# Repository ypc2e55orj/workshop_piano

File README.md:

# 簡易ピアノ

2024/01/11, Kohei Hayashi

## ディレクトリ構成

| フォルダ名 |         説明         |
| :--------: | :------------------: |
|  firmware  | MPLAB X プロジェクト |
| schematic  |  KiCad プロジェクト  |
|    docs    |         資料         |

## 必要バージョン

- MPLAB X IDE `v6.15`, xc8 `v2.45`
- KiCad `7.0`
- Microsoft Office 365 Excel

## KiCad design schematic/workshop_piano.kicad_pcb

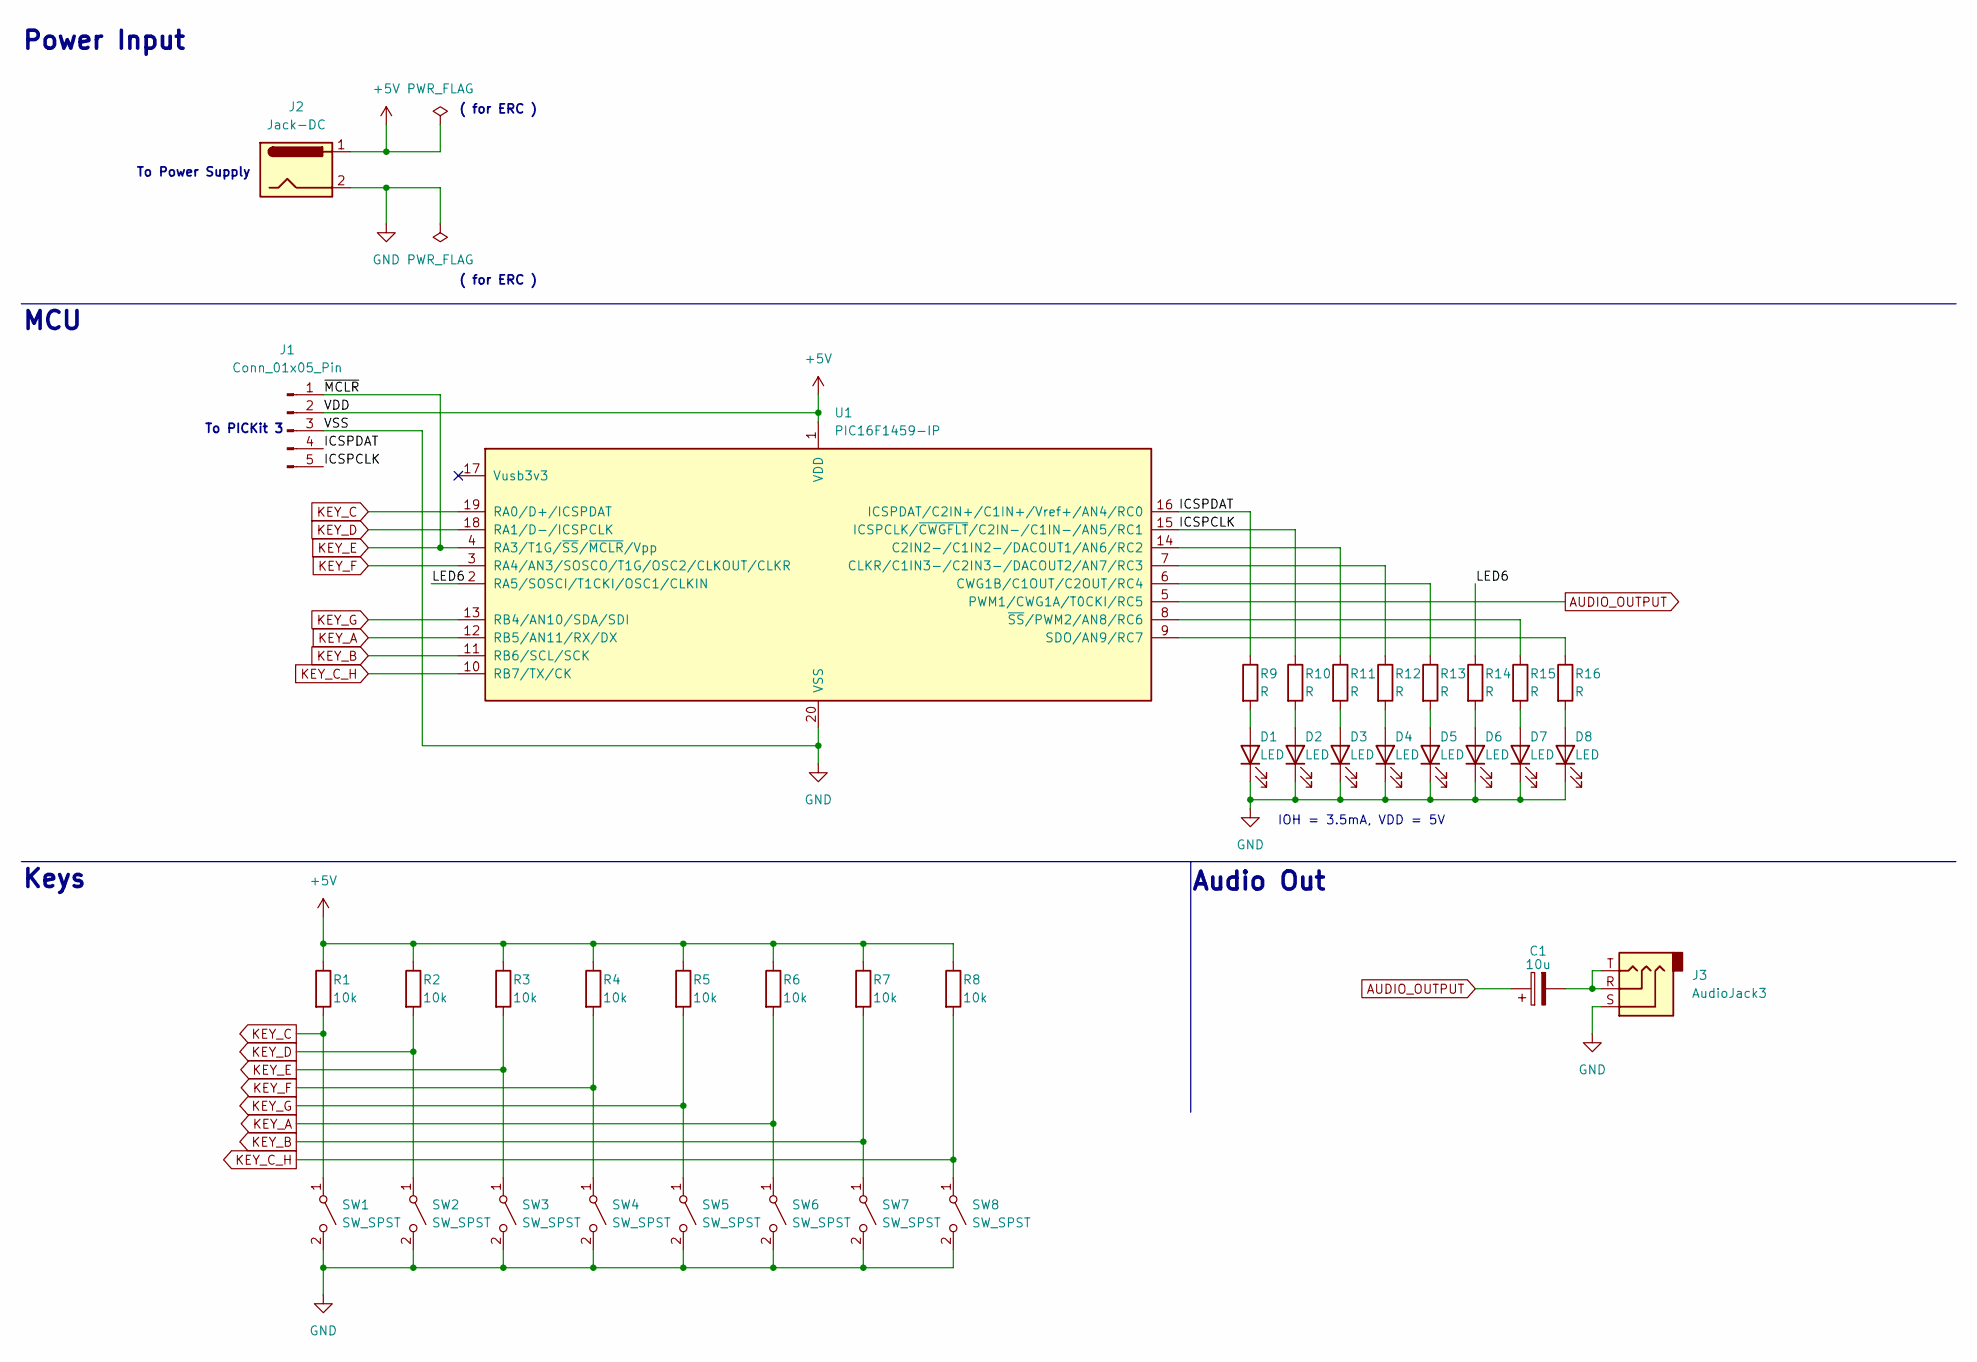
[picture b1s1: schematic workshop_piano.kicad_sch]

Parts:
C1: 10u; CP_Radial_D4.0mm_P1.50mm
D1, D2, D3, D4, D5, D6, D7, D8: LED; LED_D3.0mm
J1: Conn_01x05_Pin; PinHeader_1x05_P2.54mm_Vertical
J2: Jack-DC; BarrelJack_Horizontal
J3: AudioJack3; Jack_3.5mm_Lumberg_1503_07_Horizontal
R1, R2, R3, R4, R5, R6, R7, R8: 10k; R_Axial_DIN0204_L3.6mm_D1.6mm_P5.08mm_Horizontal
R9, R10, R11, R12, R13, R14, R15, R16: R; R_Axial_DIN0204_L3.6mm_D1.6mm_P5.08mm_Horizontal
SW1, SW2, SW3, SW4, SW5, SW6, SW7, SW8: SW_SPST; SW_PUSH-12mm
U1: PIC16F1459-IP; DIP-20_W7.62mm

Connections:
+5V: J1.2, J2.1, R1.1, R2.1, R3.1, R4.1, R5.1, R6.1, R7.1, R8.1, U1.1 (VDD)
/ICSPCLK: J1.5, R10.1, U1.15 (ICSPCLK/~CWGFLT/C2IN-/C1IN-/AN5/RC1)
/ICSPDAT: J1.4, R9.1, U1.16 (ICSPDAT/C2IN+/C1IN+/Vref+/AN4/RC0)
/LED6: R14.1, U1.2 (RA5/SOSCI/T1CKI/OSC1/CLKIN)
AUDIO_OUTPUT: C1.1, U1.5 (PWM1/CWG1A/T0CKI/RC5)
GND: D1.1 (K), D2.1 (K), D3.1 (K), D4.1 (K), D5.1 (K), D6.1 (K), D7.1 (K), D8.1 (K), J1.3, J2.2, J3.S, SW1.2 (B), SW2.2 (B), SW3.2 (B), SW4.2 (B), SW5.2 (B), SW6.2 (B), SW7.2 (B), SW8.2 (B), U1.20 (VSS)
KEY_A: R6.2, SW6.1 (A), U1.12 (RB5/AN11/RX/DX)
KEY_B: R7.2, SW7.1 (A), U1.11 (RB6/SCL/SCK)
KEY_C: R1.2, SW1.1 (A), U1.19 (RA0/D+/ICSPDAT)
KEY_C_H: R8.2, SW8.1 (A), U1.10 (RB7/TX/CK)
KEY_D: R2.2, SW2.1 (A), U1.18 (RA1/D-/ICSPCLK)
KEY_E: J1.1, R3.2, SW3.1 (A), U1.4 (RA3/T1G/~SS/~MCLR/Vpp)
KEY_F: R4.2, SW4.1 (A), U1.3 (RA4/AN3/SOSCO/T1G/OSC2/CLKOUT/CLKR)
KEY_G: R5.2, SW5.1 (A), U1.13 (RB4/AN10/SDA/SDI)
unnamed: C1.2, J3.R, J3.T
unnamed: D1.2 (A), R9.2
unnamed: D2.2 (A), R10.2
unnamed: D3.2 (A), R11.2
unnamed: D4.2 (A), R12.2
unnamed: D5.2 (A), R13.2
unnamed: D6.2 (A), R14.2
unnamed: D7.2 (A), R15.2
unnamed: D8.2 (A), R16.2
unnamed: R11.1, U1.14 (C2IN2-/C1IN2-/DACOUT1/AN6/RC2)
unnamed: R12.1, U1.7 (CLKR/C1IN3-/C2IN3-/DACOUT2/AN7/RC3)
unnamed: R13.1, U1.6 (CWG1B/C1OUT/C2OUT/RC4)
unnamed: R16.1, U1.9 (SDO/AN9/RC7)
unnamed: R15.1, U1.8 (~SS/PWM2/AN8/RC6)

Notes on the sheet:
Power Input
Keys
( for ERC )
To PICKit 3
To Power Supply
IOH = 3.5mA, VDD = 5V
Audio Out
MCU

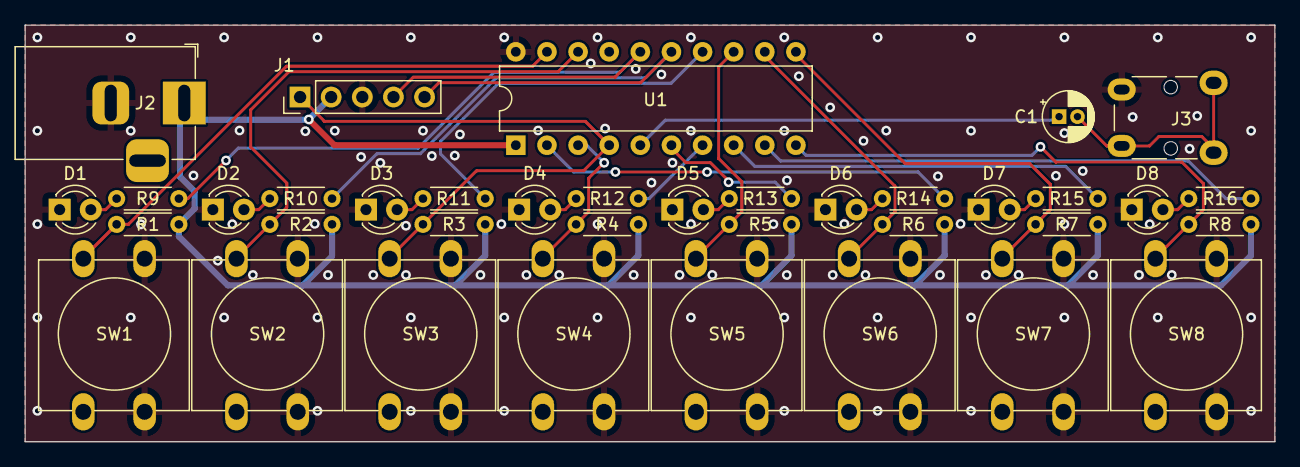
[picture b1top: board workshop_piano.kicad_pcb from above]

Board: 2 copper layers, 102.0 x 34.0 mm, 37 parts (0 on the bottom side), 28 nets.

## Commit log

2024-01-14 Update schematic
2024-01-14 Add PWM sample
2024-01-14 Add README.md
2024-01-14 Move .vscode
2024-01-14 Restore .vscode
2024-01-14 Suppress errors in vscode
2024-01-14 Change duty in isr
2024-01-14 Remove dead codes
2024-01-14 Add port operation macros
2024-01-15 Add calculator
2024-01-15 Update file associations
2024-01-16 Support four chords
2024-01-19 回路図の修正をAWに反映
2024-01-19 Remove a line
2024-01-20 出力ファイル追加
